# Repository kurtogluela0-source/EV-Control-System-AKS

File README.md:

# EV Control System (AKS)

Custom vehicle control system PCB developed for an electric vehicle project.

## Overview

The AKS (Araç Kontrol Sistemi) is a custom vehicle control and monitoring board designed for an electric vehicle platform.

The system integrates vehicle communication, telemetry, data logging, power management and control interfaces on a single embedded hardware platform.

The project was developed as part of the ElektroAydın electric vehicle team and focuses on practical embedded hardware design, vehicle communication and system integration.

## Key Features

- ATmega2560-based control architecture
- CAN Bus communication using MCP2515
- GSM telemetry using SIM800C
- SD card data logging
- DS3231 Real-Time Clock
- Relay and contactor control
- 12 V vehicle power input
- Regulated 5 V and 3.3 V power rails
- Modular communication and peripheral interfaces

## PCB Design

### 3D View

### PCB Layout

## Communication Interfaces

| Interface | Application |
|---|---|
| CAN Bus | Vehicle and BMS communication |
| UART | GSM and external peripheral communication |
| SPI | MCP2515 CAN controller and SD card |
| I2C | DS3231 Real-Time Clock |

## Hardware Architecture

The board is designed around the ATmega2560 platform and provides multiple communication and control interfaces required for electric vehicle applications.

The hardware architecture includes:

- Vehicle CAN communication
- GSM-based telemetry
- External peripheral communication
- Data logging
- Real-time clock functionality
- Relay and contactor control
- Multi-voltage power distribution
- Modular communication interfaces

## Power Architecture

The system is powered from the vehicle's 12 V electrical system.

Voltage regulation stages are used to generate the required supply rails for the control electronics and communication modules.

The board provides:

- 12 V vehicle input
- Regulated 5 V supply
- Regulated 3.3 V supply
- Power distribution for communication modules
- Decoupling and filtering for supply stability

## CAN Bus Integration

CAN Bus communication is implemented using the MCP2515 CAN controller.

The CAN interface enables communication between the AKS and other vehicle systems such as the Battery Management System (BMS).

## GSM Telemetry

A SIM800C GSM module is used for telemetry and remote data communication.

The GSM interface enables selected vehicle data to be transmitted externally when required.

## Relay and Contactor Control

The AKS includes relay control interfaces for switching vehicle systems.

These outputs can be used to control higher-power components such as vehicle contactors through low-power control signals.

## Data Logging

Vehicle data can be stored locally using an SD card interface.

The SD card communicates with the microcontroller using SPI and can be used for:

- Vehicle data logging
- Sensor recording
- CAN data storage
- System monitoring

## Real-Time Clock

A DS3231 Real-Time Clock module is connected using I2C.

The RTC provides timestamp information for logged vehicle data and system events.

## Hardware Testing

The board was evaluated through power verification, communication interface testing, peripheral integration and vehicle-level system testing.

## My Contribution

My responsibilities in the project included:

- System architecture design
- Schematic design
- PCB layout
- Component selection
- Power distribution design
- CAN communication hardware integration
- GSM telemetry hardware integration
- Relay and contactor interface design
- Peripheral interface planning
- PCB manufacturing preparation
- Hardware testing
- System integration

## Tools & Technologies

- KiCad
- ATmega2560
- Arduino Mega platform
- CAN Bus
- MCP2515
- SIM800C
- DS3231
- SPI
- UART
- I2C
- PCB Design
- Embedded Systems
- Hardware Testing
- Git
- GitHub

## Project Status

The project was designed, manufactured, tested and integrated as part of an electric vehicle development process.

The current prototype demonstrates vehicle communication, telemetry, data logging, power distribution and control interface integration.

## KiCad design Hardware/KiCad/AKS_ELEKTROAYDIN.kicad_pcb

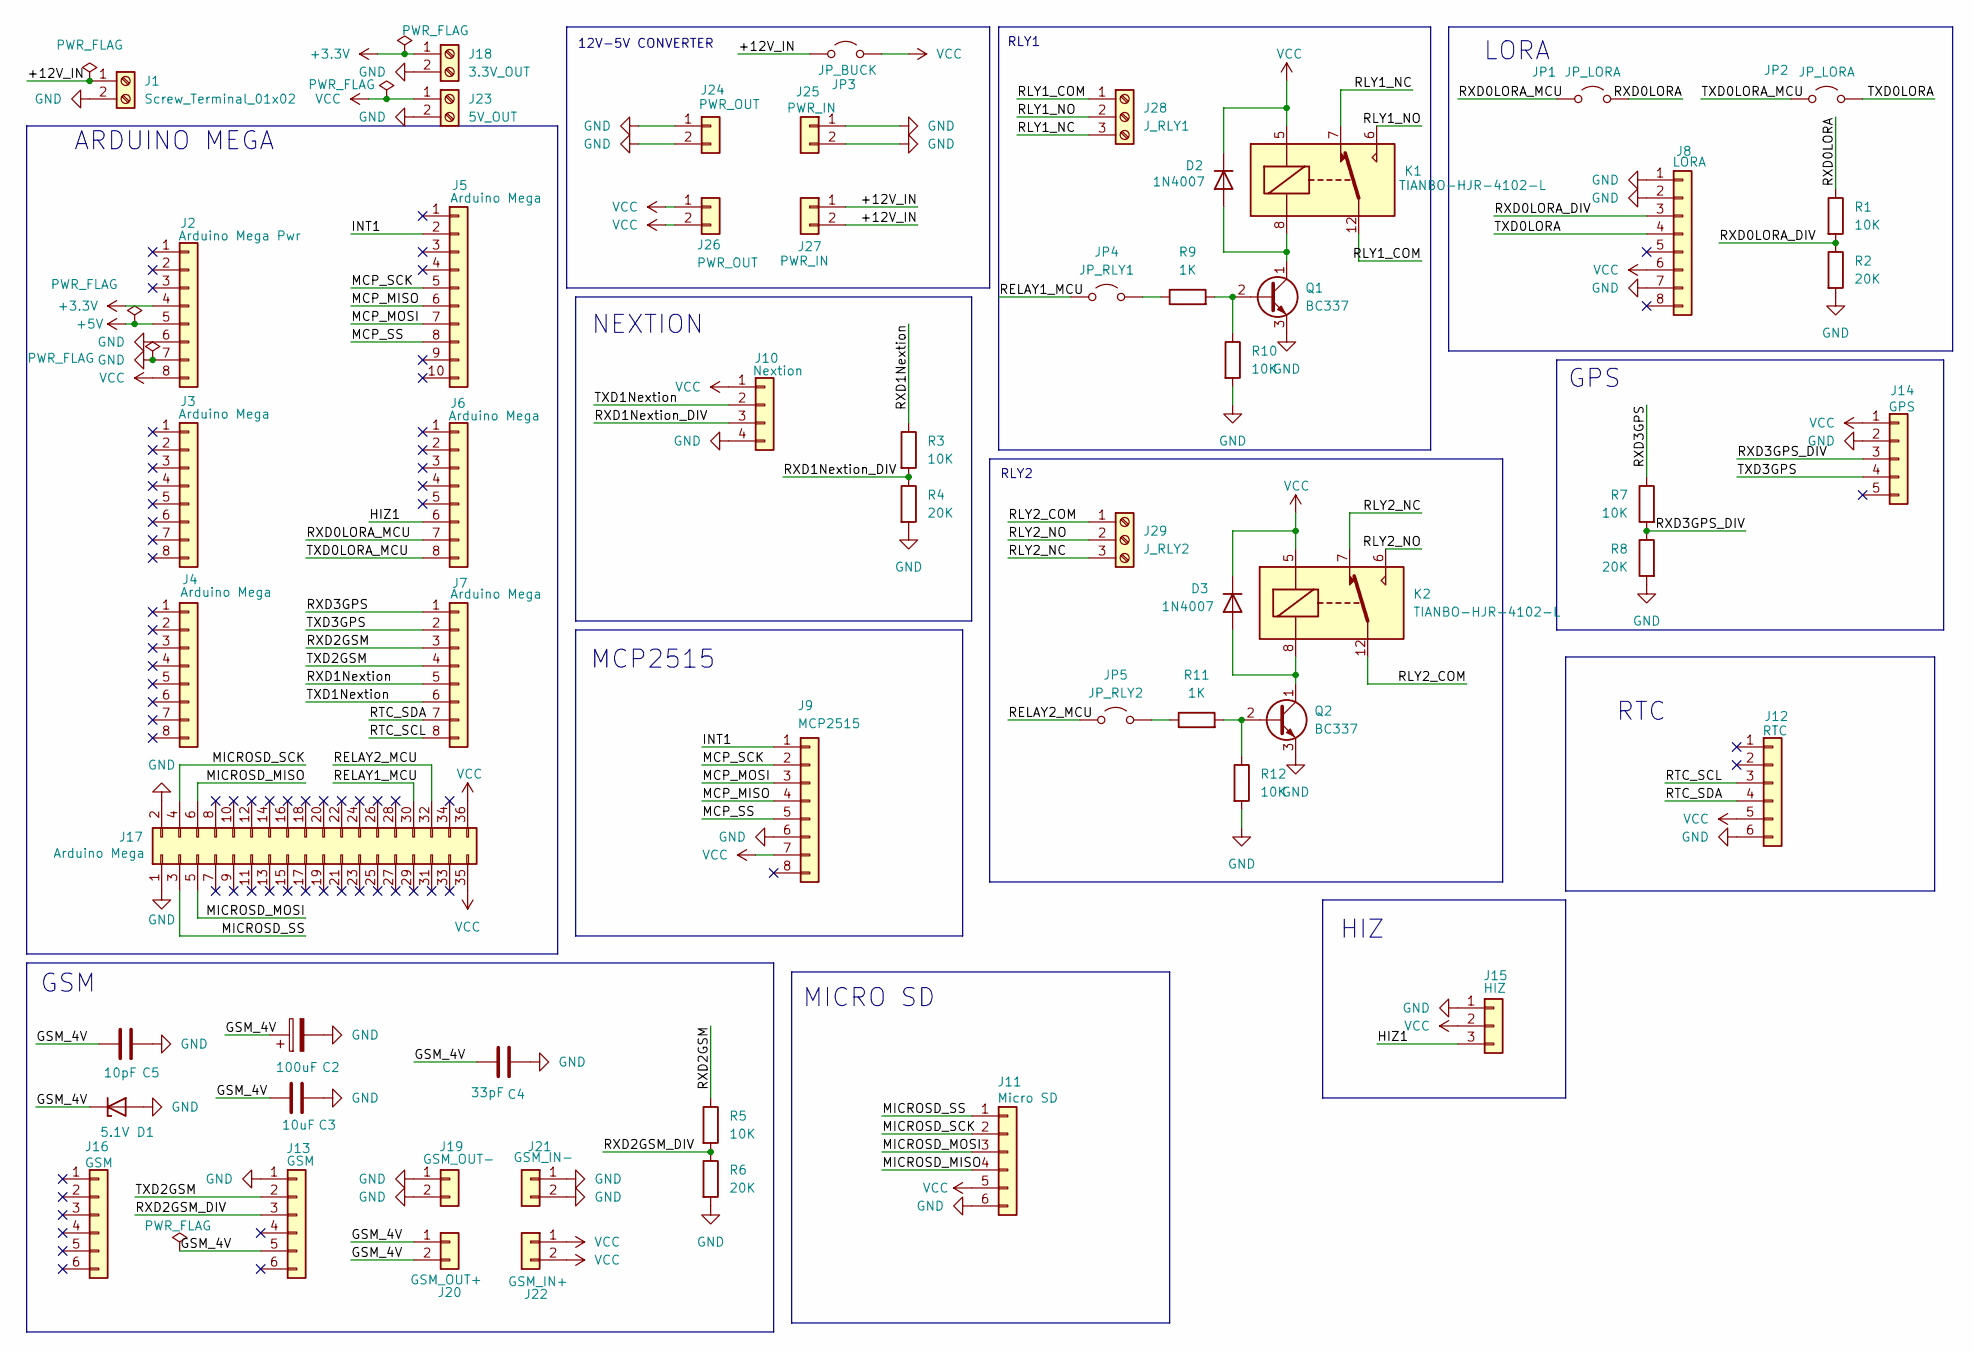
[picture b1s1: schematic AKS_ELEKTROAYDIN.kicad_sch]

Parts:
C2: 100uF; CP_Radial_D6.3mm_P2.50mm
C3: 10uF; C_Disc_D5.0mm_W2.5mm_P2.50mm
C4: 33pF; C_Disc_D5.0mm_W2.5mm_P2.50mm
C5: 10pF; C_Disc_D5.0mm_W2.5mm_P2.50mm
D1: 5.1V; D_DO-35_SOD27_P7.62mm_Horizontal
D2, D3: 1N4007; D_DO-41_SOD81_P10.16mm_Horizontal
J1: Screw_Terminal_01x02
J2: Arduino Mega Pwr; PinHeader_1x08_P2.54mm_Vertical
J3, J4, J6, J7: Arduino Mega; PinHeader_1x08_P2.54mm_Vertical
J5: Arduino Mega; PinHeader_1x10_P2.54mm_Vertical
J8: LORA; PinSocket_1x08_P2.54mm_Vertical
J9: MCP2515; PinSocket_1x08_P2.54mm_Vertical
J10: Nextion; PinSocket_1x04_P2.54mm_Vertical
J11: Micro SD; PinSocket_1x06_P2.54mm_Vertical
J12: RTC; PinSocket_1x06_P2.54mm_Vertical
J13, J16: GSM; PinSocket_1x06_P2.54mm_Vertical
J14: GPS; PinSocket_1x05_P2.54mm_Vertical
J15: HIZ; PinSocket_1x03_P2.54mm_Vertical
J17: Arduino Mega; PinHeader_2x18_P2.54mm_Vertical
J18: 3.3V_OUT; TerminalBlock_Phoenix_MKDS-1,5-2-5.08_1x02_P5.08mm_Horizont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
J19: GSM_OUT-; PinSocket_1x02_P2.54mm_Vertical
J20: GSM_OUT+; PinSocket_1x02_P2.54mm_Vertical
J21: GSM_IN-; PinSocket_1x02_P2.54mm_Vertical
J22: GSM_IN+; PinSocket_1x02_P2.54mm_Vertical
J23: 5V_OUT; TerminalBlock_Phoenix_MKDS-1,5-2-5.08_1x02_P5.08mm_Horizont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
J24, J26: PWR_OUT; PinSocket_1x02_P2.54mm_Vertical
J25, J27: PWR_IN; PinSocket_1x02_P2.54mm_Vertical
J28: J_RLY1; TerminalBlock_Phoenix_MKDS-1,5-3-5.08_1x03_P5.08mm_Horizont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
J29: J_RLY2; TerminalBlock_Phoenix_MKDS-1,5-3-5.08_1x03_P5.08mm_Horizont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
JP1, JP2: JP_LORA; PinHeader_1x02_P2.54mm_Vertical
JP3: JP_BUCK; PinHeader_1x02_P2.54mm_Vertical
JP4: JP_RLY1; PinHeader_1x02_P2.54mm_Vertical
JP5: JP_RLY2; PinHeader_1x02_P2.54mm_Vertical
K1, K2: TIANBO-HJR-4102-L; Relay_SPDT_HJR-4102
Q1, Q2: BC337; TO-92_Inline
R1, R3, R5, R7, R10, R12: 10K; R_Axial_DIN0207_L6.3mm_D2.5mm_P10.16mm_Horizontal
R2, R4, R6, R8: 20K; R_Axial_DIN0207_L6.3mm_D2.5mm_P10.16mm_Horizontal
R9, R11: 1K; R_Axial_DIN0207_L6.3mm_D2.5mm_P10.16mm_Horizontal

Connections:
+3.3V: J2.4, J18.1
+5V: J2.5
/+12V_IN: J1.1, J27.1, J27.2, JP3.1 (A)
/GSM_4V: C2.1, C3.2, C4.1, C5.1, D1.1 (K), J13.5, J20.1, J20.2
/HIZ1: J6.6, J15.3
/INT1: J5.2, J9.1
/MCP_MISO: J5.6, J9.4
/MCP_MOSI: J5.7, J9.3
/MCP_SCK: J5.5, J9.2
/MCP_SS: J5.8, J9.5
/MICROSD_MISO: J11.4, J17.6
/MICROSD_MOSI: J11.3, J17.5
/MICROSD_SCK: J11.2, J17.4
/MICROSD_SS: J11.1, J17.3
/RELAY1_MCU: J17.30, JP4.1 (A)
/RELAY2_MCU: J17.32, JP5.1 (A)
/RLY1_COM: J28.1, K1.12
/RLY1_NC: J28.3, K1.7
/RLY1_NO: J28.2, K1.6
/RLY2_COM: J29.1, K2.12
/RLY2_NC: J29.3, K2.7
/RLY2_NO: J29.2, K2.6
/RTC_SCL: J7.8, J12.3
/RTC_SDA: J7.7, J12.4
/RXD0LORA: JP1.2 (B), R1.1
/RXD0LORA_DIV: J8.3, R1.2, R2.1
/RXD0LORA_MCU: J6.7, JP1.1 (A)
/RXD1Nextion: J7.5, R3.1
/RXD1Nextion_DIV: J10.3, R3.2, R4.1
/RXD2GSM: J7.3, R5.1
/RXD2GSM_DIV: J13.3, R5.2, R6.1
/RXD3GPS: J7.1, R7.1
/RXD3GPS_DIV: J14.3, R7.2, R8.1
/TXD0LORA: J8.4, JP2.2 (B)
/TXD0LORA_MCU: J6.8, JP2.1 (A)
/TXD1Nextion: J7.6, J10.2
/TXD2GSM: J7.4, J13.2
/TXD3GPS: J7.2, J14.4
GND: C2.2, C3.1, C4.2, C5.2, D1.2 (A), J1.2, J2.6, J2.7, J8.1, J8.2, J8.7, J9.6, J10.4, J11.6, J12.6, J13.1, J14.2, J15.1, J17.1, J17.2, J18.2, J19.1, J19.2, J21.1, J21.2, J23.2, J24.1, J24.2, J25.1, J25.2, Q1.3 (E), Q2.3 (E), R2.2, R4.2, R6.2, R8.2, R10.2, R12.2
unnamed: D2.2 (A), K1.8, Q1.1 (C)
unnamed: D3.2 (A), K2.8, Q2.1 (C)
unnamed: JP4.2 (B), R9.1
unnamed: JP5.2 (B), R11.1
unnamed: Q1.2 (B), R9.2, R10.1
unnamed: Q2.2 (B), R11.2, R12.1
VCC: D2.1 (K), D3.1 (K), J2.8, J8.6, J9.7, J10.1, J11.5, J12.5, J14.1, J15.2, J17.35, J17.36, J22.1, J22.2, J23.1, J26.1, J26.2, JP3.2 (B), K1.5, K2.5

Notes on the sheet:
GPS
12V-5V CONVERTER
MCP2515
RTC
RLY1
ARDUINO MEGA
NEXTION
LORA
HIZ
MICRO SD
GSM
RLY2

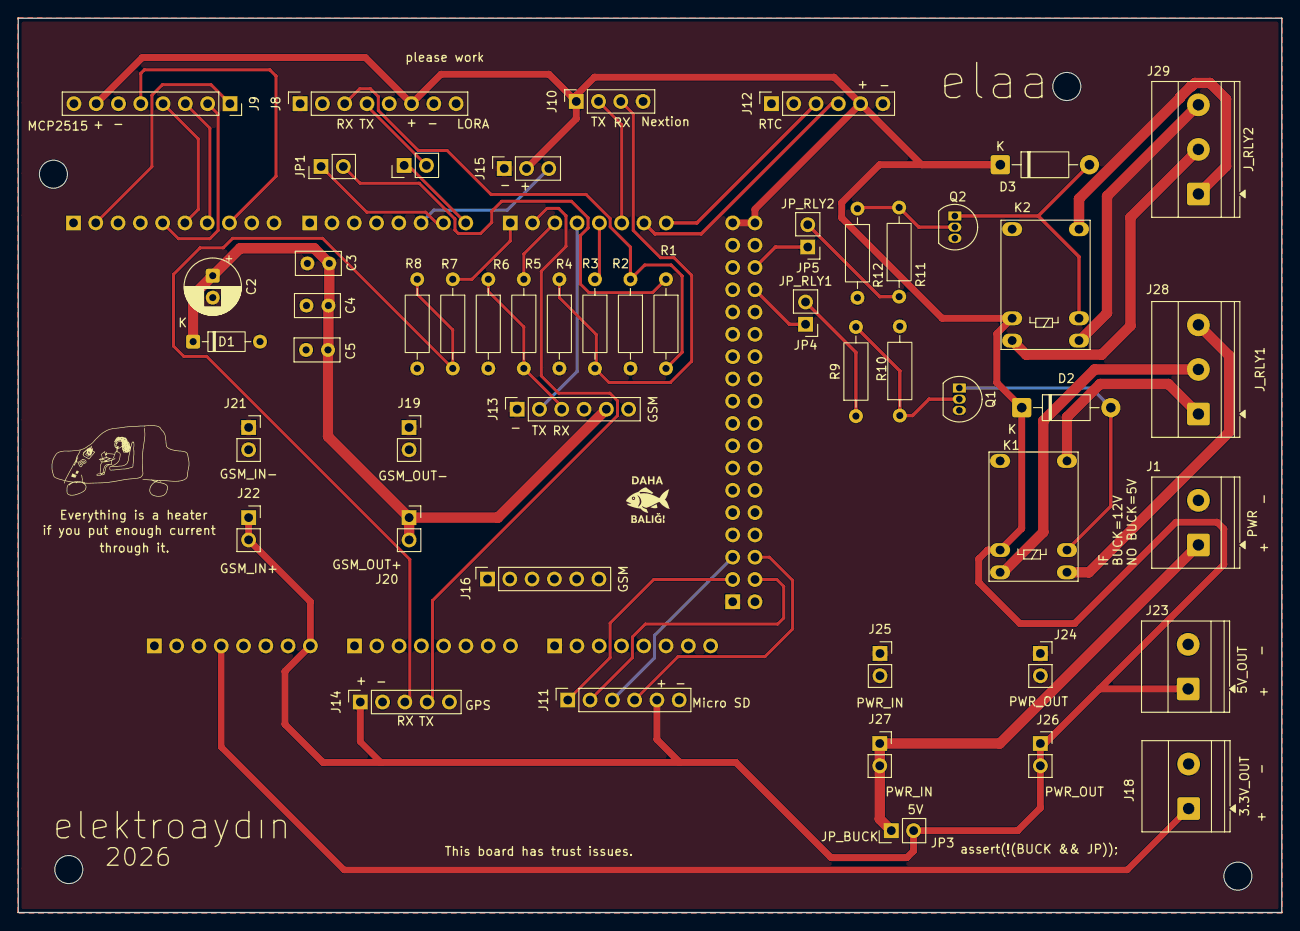
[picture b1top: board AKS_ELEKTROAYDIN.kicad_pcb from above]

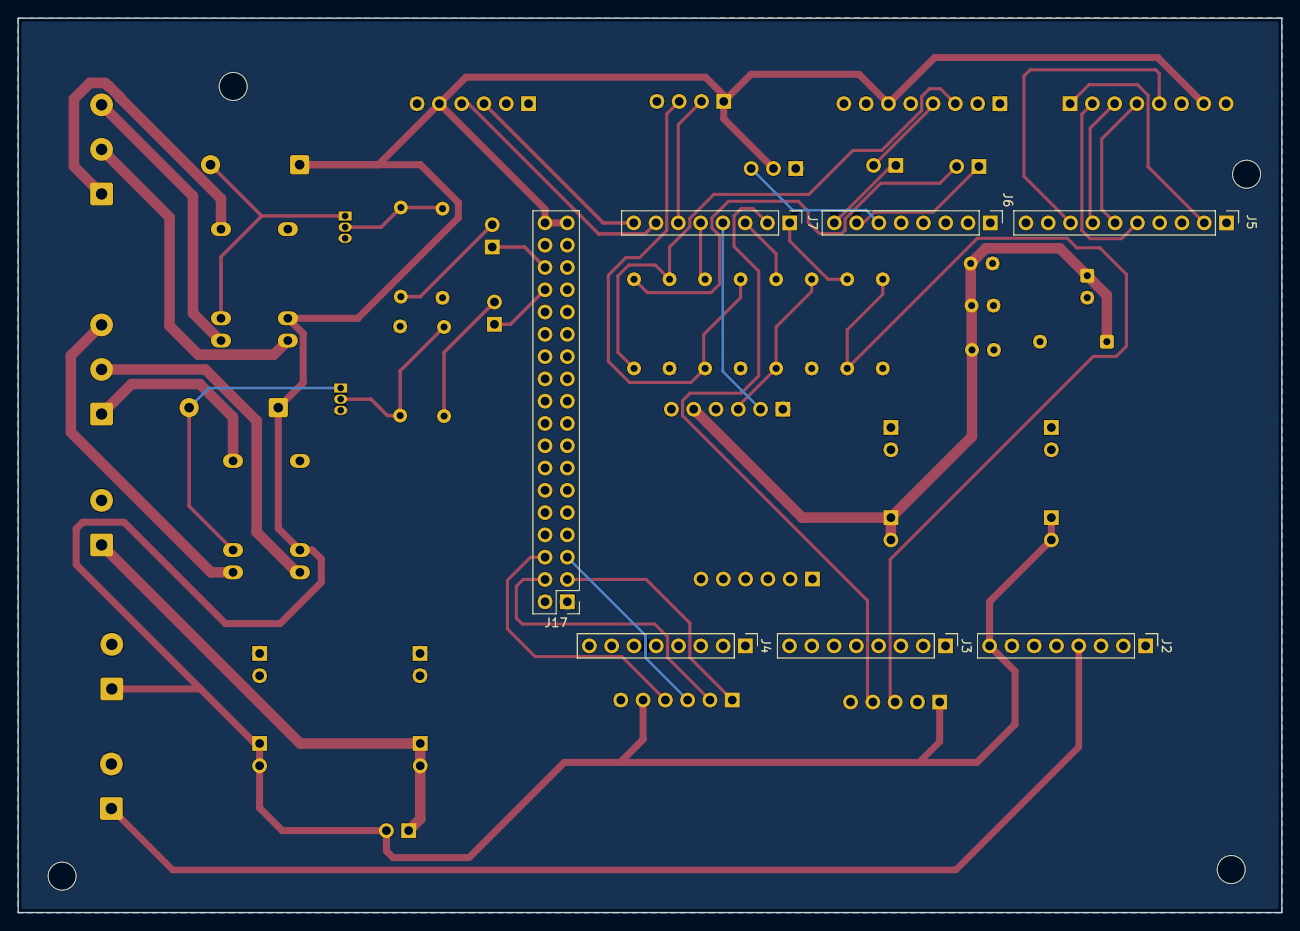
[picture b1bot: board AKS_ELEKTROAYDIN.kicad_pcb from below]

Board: 2 copper layers, 144.0 x 101.9 mm, 57 parts (7 on the bottom side), 45 nets.
